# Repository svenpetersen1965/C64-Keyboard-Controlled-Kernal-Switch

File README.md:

# C64-Keyboard-Controlled-Kernal-Switch
This is a Kernal Switch for the Commodore C64, which does not requires any case modifications. The Kernal is selected by holing RESTORE and pushing a number key. 

Jusrt holding RESTORE for several seconds will reset the C64. The index of selected Kernal is stored non-volatile, so the last selection will be executed after a power on.

Find some info on the required cable making <a href="http://tech.guitarsite.de/cable_making.html">on my website</a>

Watch the introduction on youtube: https://youtu.be/pfJxfMYcyzs

The Kernal Switch works in conjuctuion with a Kernal Adaptor:

https://github.com/svenpetersen1965/C64-Kernal-Adaptor-Switch-short-board- for ASSY 250469 Mainboards

https://github.com/svenpetersen1965/C64-Kernal-Adapter-Switch-Long-Board for all other Mainboards

I want to thank MindFlareRetro (https://www.youtube.com/channel/UCBbbiZC2YodIp2Pi-lywG-A/featured) for reviewing my documentation.

# Known Issue
Solved:

Some games/software require an EXROM-Reset, because they change the reset and/or NMI vector. Then the reset does not jump, where it should jump. It even seems, that the problem is persistent even after a power off. Don't panic... your C64 will function again, later. It seems, those games leave some traces in RAM, which have to get lost after being powered off for a while. 

This can be solved by also holding EXROM low while the reset. One of the two reserved IO pins in the pin header can serve to assert EXROM. The software will be changed and the result will be tested.

The problem stated above is some kind of copy protection and is described in detail here: http://tech.guitarsite.de/cbm80.html 

## Software Rev. 0.1
This software fixes the issue described above. An aditional connection is required. J4, Pin 5 (RS1) has to be connected to the EXROM signal (Expansion port, Pin 9, which can easily be accessed inside the C64) via a 220R resistor. The documentation has been updated.

## Software Rev. 0.2
This software makes use of the last free GPIO pin on J4 (Pin 6, "RS2" on Rev. 0 or "RESIO" on Rev. 1). A LED, that is connected there, will be on most of the time. When holding the RESTORE key and the time (about 3 seconds) is elapsed to initiate a "normal" reset, the LED switch off for a short time. Holding RESTORE for 5 seconds will initiate an EXROM reset. The LED signal should help to release the RESTOR key in time for a normal reset.

Board Rev. 1 already provides a current limiting resistor for an LED (R9). A value of 330R is suitable for a red, green or yellow LED, 50R is suitable for a blue LED.

Board Rev. 0 does not provide this resistor. Here, a resistor has to be installed in the LED cable. DO NOT try to connect an LED without a resistor!!! Theis can damage the LED and also the processor of the Kernal Switcher.  

# REV. 1
Revision 1 is released. The hardware Rev. 1 is tested ok. The documentation is finished.

# Calculation of the component prices
The BOM v1.1 was calculated. The total price of the components is 5.98€, which does not incluse any shiping fees. The cables were not calculated.

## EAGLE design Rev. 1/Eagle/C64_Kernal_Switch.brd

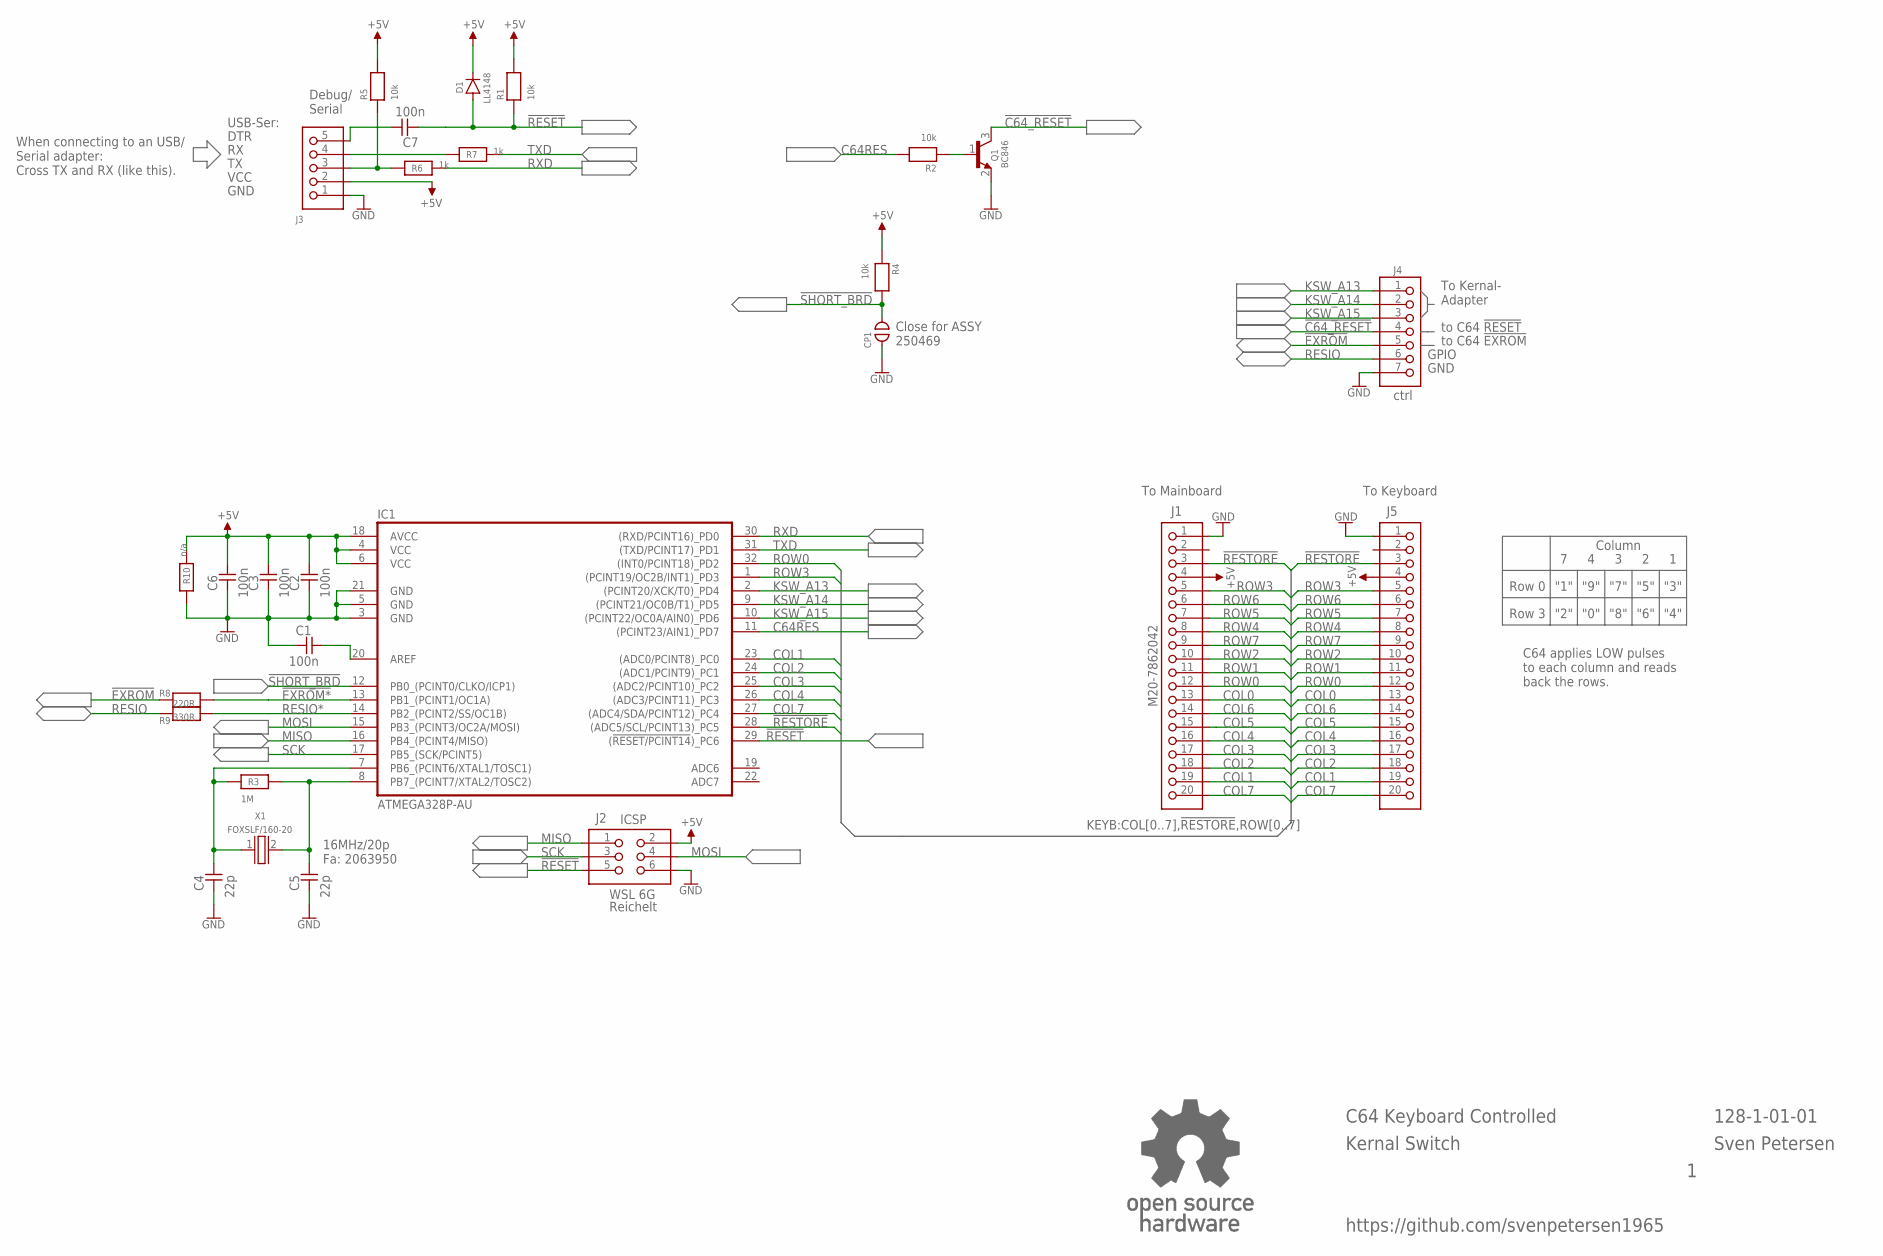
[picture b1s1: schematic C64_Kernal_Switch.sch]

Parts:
C1, C2, C3, C6, C7: 100n; 0805
C4, C5: 22p; 0805
CP1: OPEN; CP_OP
D1: LL4148; SOD80C
IC1: ATMEGA328P-AU; QFP80P900X900X120-32N
J1: M20-7862042; C64_KEYBOARD
J2: WSL 6G; 2X03WV
J3: n/a; 1X05
J4: PINHD-1X7; 1X07
J5: PINHD-1X20; 1X20
Q1: BC846; SOT23
R1, R2, R4, R5: 10k; 0805
R3: 1M; 0805
R6, R7: 1k; 0805
R8: 220R; 0805
R9: 330R; 0805
R10: n/a; 0805
U$55: OPEN_SOURCE_HW; OPENHW
X1: FOXSLF/160-20; HC49SLF

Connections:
!C64_RESET: J4.4, Q1.3 (C)
!EXROM: J4.5, R8.1
!EXROM*: IC1.13 (PB1_(PCINT1/OC1A)), R8.2
!RESET: C7.1, D1.A, IC1.29 ((!RESET/PCINT14!)_PC6), J2.5, R1.1
!RESTORE: IC1.28 ((ADC5/SCL/PCINT13)_PC5), J1.3, J5.3
!SHORT_BRD: CP1.2, IC1.12 (PB0_(PCINT0/CLKO/ICP1)), R4.2
+5V: C2.2, C3.2, C6.2, D1.K, IC1.4 (VCC), IC1.6 (VCC), IC1.18 (AVCC), J1.4, J2.2, J3.2, J5.4, R1.2, R4.1, R5.2, R10.2
C64RES: IC1.11 ((PCINT23/AIN1)_PD7), R2.2
COL0: J1.13, J5.13
COL1: IC1.23 ((ADC0/PCINT8)_PC0), J1.19, J5.19
COL2: IC1.24 ((ADC1/PCINT9)_PC1), J1.18, J5.18
COL3: IC1.25 ((ADC2/PCINT10)_PC2), J1.17, J5.17
COL4: IC1.26 ((ADC3/PCINT11)_PC3), J1.16, J5.16
COL5: J1.15, J5.15
COL6: J1.14, J5.14
COL7: IC1.27 ((ADC4/SDA/PCINT12)_PC4), J1.20, J5.20
GND: C1.1, C2.1, C3.1, C4.1, C5.1, C6.1, CP1.1, IC1.3 (GND), IC1.5 (GND), IC1.21 (GND), J1.1, J2.6, J3.1, J4.7, J5.1, Q1.2 (E), R10.1
KSW_A13: IC1.2 ((PCINT20/XCK/T0)_PD4), J4.1
KSW_A14: IC1.9 ((PCINT21/OC0B/T1)_PD5), J4.2
KSW_A15: IC1.10 ((PCINT22/OC0A/AIN0)_PD6), J4.3
MISO: IC1.16 (PB4_(PCINT4/MISO)), J2.1
MOSI: IC1.15 (PB3_(PCINT3/OC2A/MOSI)), J2.4
unnamed: C4.2, IC1.7 (PB6_(PCINT6/XTAL1/TOSC1)), R3.1, X1.1
unnamed: C5.2, IC1.8 (PB7_(PCINT7/XTAL2/TOSC2)), R3.2, X1.2
unnamed: C1.2, IC1.20 (AREF)
unnamed: Q1.1 (B), R2.1
unnamed: C7.2, J3.5
unnamed: J3.4, R7.1
unnamed: J3.3, R5.1, R6.1
RESIO: J4.6, R9.1
RESIO*: IC1.14 (PB2_(PCINT2/SS/OC1B)), R9.2
ROW0: IC1.32 ((INT0/PCINT18)_PD2), J1.12, J5.12
ROW1: J1.11, J5.11
ROW2: J1.10, J5.10
ROW3: IC1.1 ((PCINT19/OC2B/INT1)_PD3), J1.5, J5.5
ROW4: J1.8, J5.8
ROW5: J1.7, J5.7
ROW6: J1.6, J5.6
ROW7: J1.9, J5.9
RXD: IC1.30 ((RXD/PCINT16)_PD0), R6.2
SCK: IC1.17 (PB5_(SCK/PCINT5)), J2.3
TXD: IC1.31 ((TXD/PCINT17)_PD1), R7.2

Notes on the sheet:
C64 Keyboard Controlled
128-1-01-01
Sven Petersen
ICSP
Reichelt
16MHz/20p Fa: 2063950
USB-Ser:
DTR
VCC
GND
Debug/ Serial
Column
Row 0
Row 3
"3"
"5"
"7"
"9"
"1"
"2"
"0"
"8"
"6"
"4"
To Kernal- Adapter
to C64 !RESET
To Mainboard
To Keyboard
Close for ASSY 250469
C64 applies LOW pulses to each column and reads back the rows.
GPIO
Kernal Switch
to C64 !EXROM
ctrl
When connecting to an USB/ Serial adapter: Cross TX and RX (like this).
https://github.com/svenpetersen1965

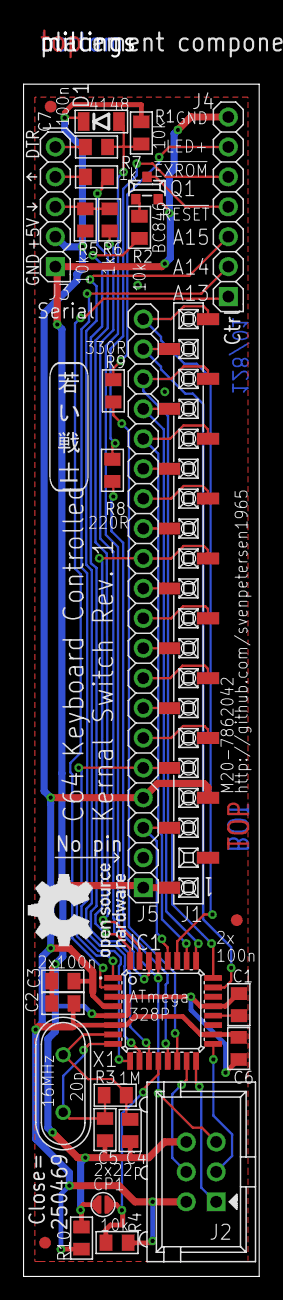
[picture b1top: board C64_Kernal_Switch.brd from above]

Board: 2 copper layers, 20.0 x 106.3 mm, 34 parts (0 on the bottom side), 42 nets.

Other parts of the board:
U$44: 2LAYER
U$45, U$46, U$47: SMD_REF_R1MM
U$52: PCB-TITLE/
U$54: SVEN_TAG

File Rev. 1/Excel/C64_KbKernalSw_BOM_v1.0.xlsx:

C64 Keyboard Controlled Kernal Switch Rev. 1
Bill of Material Rev. 1.0
Pos. | Qty | Value | Footprint | Ref.-No. | Comment
1 | 1 | 128-2-01-01 | 2 Layer | PCB Rev. 1 | 2 layer, Cu 35µ, HASL, 101.2mm x 20.0mm, 1.6mm FR4
2 |  | copper structure on pcb |  | CP1 | no part, open Cutpad, close for ASSY250469
3 | 1 | 1x20 | 1X20 | J5 | pin header 1x20pin, 2.54mm pitch
4 | 1 | 1x7 | 1X07 | J4 | pin header 1x7pin, 2.54mm pitch
5 | 5 | 100n | 0805 | C1, C2, C3, C6, C7 | SMD capacitor
6 | 4 | 10k | 0805 | R1, R2, R4, R5 | SMD resistor, 5% or better
7 | 1 | 1M | 0805 | R3 | SMD resistor, 5% or better
8 | 3 | 1k | 0805 | R6, R7, R10 | SMD resistor, 5% or better
9 | 2 | 22p | 0805 | C4, C5 | SMD capacitor
10 | 1 | ATMEGA328P-AU | QFP80P900X900X120-32N | IC1 | Atmel/Micro Chip, e.g. Farnell 2443176
11 | 1 | BC846B | SOT23 | Q1 | SMD transistor
12 | 1 | 16 MHz/20pF quarz | HC49SLF | X1 | e.g. Fox Electronics, FOXSLF/160-20, Farnell 2063950
13 | 1 | LL4148 | SOD80C | D1 | SMD diode
14 | 1 | M20-7862042 | M20-7862042 | J1 | Harwin, e.g. Farnell 1256661
15 | 1 | WSL 6G | 2X03WV | J2 | box pin header, 2x3pin, 2.54mm pitch
16 | 1 | 1x5 | 1X05 | J3 | pin header 1x5pin, 2.54mm pitch
17 | 2 | 220R | 0805 | R8, R9 | SMD resistor, 5% or better
 |  | Rev. History
Pos. |  | Rev. 0 -> Rev. 1
1 |  | PCB revision
4 |  | Now 7 pin
8 |  | R10 is new
17 |  | new

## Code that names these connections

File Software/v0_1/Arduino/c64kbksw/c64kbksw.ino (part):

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const int  NumKernal = 8;            //This is the highest valid Kernal number
 
/* pin definitions */
const int row0 = 2;         // Row signal, input, active low, INT0
const int row3 = 3;         // Row signal, input, active low, INT1
const int KSW_A13 = 4;      // output, A13 to kernal adaptor/switch
const int KSW_A14 = 5;      // output, A14 to kernal adaptor/switch
const int KSW_A15 = 6;      // output, A15 to kernal adaptor/switch
const int C64RESET = 7;     // output, RESET signal for the C64
const int col1 = A0;        // input, column signal, active low
const int col2 = A1;        // input, column signal, active low
const int col3 = A2;        // input, column signal, active low
const int col4 = A3;        // input, column signal, active low
const int col7 = A4;        // input, column signal, active low
const int nRESTORE = A5;    // input, RESTORE key, active low
const int nSHORT_BRD = 8;   // input, short board jumper
const int nEXROM = 9;       // /EXROM Pin connected to pin header J4, pin 5 
const int RSVD  = 10;       // reserved. Pin connected to pin header J4, pin 6
const int Restore_Count = 1500; // count appr. 2 seconds for RestoreKey before Reset
const int EXROM_Count = 3000;   // limit for EXROM reset

/* other constants */
#define EEPROMAddr 0        // EEPROM Address of last kernal selection
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byte KOffset = 0;           // offset for kernal number
byte KNumber = 0;           // Kernal number
byte KAddr = 0;             // Address bits for Kernal
bool RestoreKey = 0;        // holds the info, if the restore key is pressed 
bool oldRestoreKey = 0;     // remeber the old status to compare
int  countup = 0;           // counter for restore key time measurement
byte key = 128;             // calculate the Key
int  KMax;                  // holds the highest Kernal Number


/* Data Exchange variables for ISR (have to be volatile) */
volatile bool NumPressed = 0;  // ISR flag for number pressed
volatile bool NumOdd = 0;      // ISR flag for odd numbers. Row0 => odd numbers, Row3 => even numbers
volatile byte ColData = 0x1F;  // column data, read from PORTD

/* in case, the kernal switch switches to a memory slot without a proper kernal software
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int scan_cnt;           // 5000 miliseconds without scan changing to kernal #1 and resetting
int scan_found;         // flag for keybioard activity detected
byte inactive = 0;      // keyboard scan inactive: 1 -> inactive, 0 = active
bool exrom_mode = 0;    // exrom reset: 0 => no, 1 => yes

void setup() {
  /* keyboard scan signals */
  pinMode( row0, INPUT_PULLUP);  // pullup required for MOS logic
  pinMode( row3, INPUT_PULLUP);  // pullup required for MOS logic
  pinMode( col1, INPUT_PULLUP);  // pullup required for MOS logic
  pinMode( col2, INPUT_PULLUP);  // pullup required for MOS logic
  pinMode( col3, INPUT_PULLUP);  // pullup required for MOS logic
  pinMode( col4, INPUT_PULLUP);  // pullup required for MOS logic
  pinMode( col7, INPUT_PULLUP);  // pullup required for MOS logic
  pinMode( nRESTORE, INPUT_PULLUP);  // pullup required for MOS logic
  pinMode( nEXROM, INPUT );      // it needs to be high impedance, will switch to LOW and OUTPUT when required.
  digitalWrite( nEXROM, HIGH );
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    inactive = 0;
    EEPROM.write(EEPROMAddr+1, inactive);
  }
  exrom_mode = 0;                               // initialize exrom mode (for reset). 0 = no exrom reset
  
  KAddr = KNumber - 1 + KOffset; // Calculate the address bits.
  // For long boards, it should be between 0 and 7,
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  
  /* Control outputs (for Kernal Adaptor and C64) */
  SetAddressBits( KAddr );        // set the MS address bits for the kernal ROM
  pinMode( KSW_A13, OUTPUT );     // make it an output   
  pinMode( KSW_A14, OUTPUT );     // make it an output
  pinMode( KSW_A15, OUTPUT );     // make it an output
  digitalWrite( C64RESET, LOW );  // no reset for the C64
  pinMode( C64RESET, OUTPUT );    // make it an output

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    scan_cnt = 0;
  }
      
  attachInterrupt(digitalPinToInterrupt(row0), ISR_row0, LOW); 
  attachInterrupt(digitalPinToInterrupt(row3), ISR_row3, LOW);
  
  Serial.begin(9600);  // start serial interface
  /* output status etc. */
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  digitalWrite( C64RESET, HIGH );                            // issue a reset pulse for the C64
  delay( 100 );                                              // 100ms delay
  if (exrom_mode == 1) {
    digitalWrite( nEXROM, LOW );                             // exrom pin low
    pinMode( nEXROM, OUTPUT );                               // and output
  }
  delay( 300 );                                              // pulse duration: 100+300ms
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  if (exrom_mode == 1) {
    delay( 300 );                                            // EXROM should be 300ms longer LOW than RESET
    pinMode( nEXROM, INPUT );                                // and input = high impedance (HIZ)
    digitalWrite( nEXROM, HIGH );                            // exrom pin high
  }
  if ((recover_empty == true) && (inactive == 0)) {
    scan_cnt = ScanDelay;                                    // reset scan countdown
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  if (NumPressed == 0) {                  // only process info, after the flag was reset by main routine
     ColData = PINC & 0x1F;               // read the columns
     scan_found = true;                   // any activity here indicates a working kernal
     NumOdd = 1;                          // row0 has the odd numbers
     if ((ColData != 0x1F) && (ColData !=0)) {               // only set the flag, when a number is pressed 
       NumPressed = 1;
     }  
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  if (NumPressed == 0) {                  // only process info, after the flag was reset by main routine
     ColData = PINC & 0x1F;               // read the columns
     scan_found = true;                   // any activity here indicates a working kernal
     NumOdd = 0;                          // row3 has the even numbers
     if ((ColData != 0x1F) && (ColData !=0)) { // only set the flag, when a number is pressed 
       NumPressed = 1;
     }  
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          exrom_mode = 0;
        }
     }
     RestoreKey = 0;                      // in case the reading is HIGH, the Restore key is not pressed
     countup = 0;                         // restart the count down
  }
  else {
    RestoreKey = 1;                       // in case the restore is pressed, count up
    if (countup++ > EXROM_Count) {        // time limit for EXROM reached?
       exrom_mode = 1;                    // activate EXROM mode
       Serial.println("EXROM mode: Restore key => Reseting the C64");
       ResetC64();                        // reset the C64
       RestoreKey = 0;                    // restart the restore key
       countup = 0;                       // restart the count down
       exrom_mode = 0;                    // reset EXROM mode
    }
  }

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
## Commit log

2019-07-05 Initial upload
2019-07-06 Add files via upload
    Reviewed version
2019-07-08 Create LICENSE
2019-07-25 Revision 1
    Documentation is preliminary. The hardware is untested.
2020-01-06 Firmware release v0.2
    Firmware v0.2 uses the remaining GPIO on J4 for signalliting the reset on a power LED. This is normally on. When pressing RESTORE for about 3 seconds, the LED will switch off for a short time, indica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
2020-01-07 Add files via upload
    the *.elf file now contains the flash programming data
2020-01-15 Rev. 1 Documentation released
    The final documentation is released
2020-01-15 not required
2020-06-09 Calculation of the copmponent prices added
2020-08-08 Silk Screen Update
2020-08-16 picknplace in mm and inch
